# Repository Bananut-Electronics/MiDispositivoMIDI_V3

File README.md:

<h1 align="center"> ⭐️ MiDispositivoMIDI V3 ⭐️ </h1>

*This repository is no longer officially maintained but feel free to open a pull request with your contribution. As we ran out of devices, we don't sell it anymore, but if you you want one you can find here all the schematics, manuals, documentations and code to build your own.*
<!-- ALL-CONTRIBUTORS-BADGE:START - Do not remove or modify this section -->

<!-- ALL-CONTRIBUTORS-BADGE:END -->

<p align="center">

<p align="center">
  Connect our device to your computer and start making music! Totally Plug&Play without any extra software, just your favourite MIDI sequencer (Logic, Ableto, Nuendo). It is not only a great tool for making music and experimenting, you can also use it to learn more about electronics, programming and Arduino. You have tons of code examples ready to load, but if you feel up to it, you can also contribute with your code. And last but not least! It is open source! You can either buy it at our website, our build it yourself, all the schematics and code are available in this repository.
  <p align="center">
  
</p>
</p>

---

<h2 align="center">❤️ Follow us! ❤️</h2>
<p align="center">

</p>

---

<h2 align="center">💶 Want to buy the product? 💶</h2>

<p align="center">
  
</p>

---

<h2 align="center">📗 Index 📗</h2>

<p align="center">
  <a href="#about-us">About us</a> •
  <a href="#midispositivomidi-v3">MiDispositivoMIDI V3</a> •
  <a href="#documentation">Documentation</a> •
  <a href="#expansions">Expansions</a> •
  <a href="#faq">FAQ</a> •
  <a href="#contributing">Contributing</a> •
  <a href="#license">License</a>
</p>

---

# About us
Hi! We are BanaNut Electronics and we develop software and hardware for Arduino with educational purposes. We were born at the UPM University in Madrid during 2013 and we haven't stopped ever since.

<center>

|      LightWand Kosmonaut V2      |  MiDispositivoMIDI V3 |
|:-------------:|:------:|
|   |  |

</center>

---

Everything started with the first version at the Polytechnical University of Madrid (UPM) in 2013. We were a couple of young students interested in music and electronics, and we came up with this idea. We started reusing some hardware, mainly found at SparkFun's website, but only one year later, we had the second version that was fully designed by us. After some trial and error and feedback from users and friends, we released this third version V3 in 2017. We not only released the code, but also we started producing devices and selling them on the internet, first in our web and later on at Tindie.com store.

During the years, the different versions of MiDispositivoMIDI have been used by many people, engineers, musicians and even kids. We gave some workshops at UPM Madrid for students in Electrical and Telecommunications Engineering, where we gave all the materials and the students had to solder, assembly and code the device.

<p align="center">
  
</a>

---

# MiDispositivoMIDI V3
We are proud to present the MiDispositivoMIDI V3, which is the latest version we have out in the market (Jan 2019). MiDispositivoMIDI is an open source MIDI controller based on Arduino. In other words, its a small device with tons of LEDs and buttons, that you can connect to your computer to, in example, make music. Our device works with the MIDI protocol, a very well known protocol used in the music industry. You can just plug our device and start using it with your favourite DAW, such as Logic, Ableton or Cubase. No other extra softare is needed.

If you are also interested in programming and electronics, this device offer you a great tool to learn by example. You can also use it to prototype and play around. And also, since it is open source you can fully costumize it to your needs. If you don't know much about coding, just load the codes that we provide, and use them. But if you like coding, you can also publish your code with new features or improvements for others to use.

<p align="center">

<p align="center">

These are the features of our device:
* Plug & Play MIDI device.
* Open source based on Arduino.
* Have 16 pad buttons in a 4x4 matrix.
* Have 2 lateral buttons.
* Have RGB leds with 256 levels of intensity of each color.
* Micro USB connection.
* Dimensions of 10x10 cm.
* Modular design. Connect up to 4 devices.
* Fully compatible with Logic, Ableton or Cubase.

<p align="center">
  
</a>

We invite you to check our YouTube channel, where we post videos about our devices. You can also follow other social networks such as Instagram o Facebook.

* https://www.youtube.com/watch?v=3QnzLwpbpRE&t
* https://www.youtube.com/watch?v=8WFfShg-0Dk
* https://www.youtube.com/watch?v=2y8fhmTmedI
* https://www.youtube.com/watch?v=TsuVpFoLFyI

---

# Documentation

We provide a C++ Arduino library that you can use with our device, that simplifies the tasks of handling the LEDs and buttons. The code is self documented, but we have also written a nice Wiki page where you can find more information about the hardware, some hints about MIDI protocol and some low level software examples in Arduino, that will allow you to understand how it works:
* Wiki: https://github.com/Bananut-Electronics/MiDispositivoMIDI_V3/wiki

TODO: Write some nice code snippets
```cpp
//TODO
```

---

# Expansions

Our device has a modular design, which means that with the same hardware, you can add modules to convert it into a bigger controller. For example, if you put four MiDispositivoMIDI V3 into a 8x8 configuration, you will have 64 buttons. All this can be done using the same hardware and with very few modificatons in the code. Note that you can also replace a 4x4 button matrix by a 4x4 potentiometer matrix, but this feature is not implemented yet.

<p align="center">

## 4x16 Configuration

You can connect 4 MiDispositivoMIDI V3 in a 4x16 configuration to get the following. With something like this, you can, for example, create an step sequencer. See this video for an example:
* https://www.youtube.com/watch?v=bYyvVDn-gKs

<p align="center">
  
</a>

## 8x8 Configuration
Same as before, you can connect the devices with a different configuration. Note that the connections are done under the PCB with an extra PCB, so no extra wiring is needed.

<p align="center">
  
</a>

## 4x8 Configuration
TODO

## Potentiometer Expansion
TODO

---

# FAQ

Feel free to send us a mail to bananutelectronics@gmail.com if you have any question, but read before our FAQ since there are some common issues that can be fixed quite easily:

* **I can't load code to my device. Why?** Make sure that in the Arduino IDE boards section (Tool->Boards) you have selected "Arduino Leonardo"
* **I was playing with some code, and now the device is gone form the serial port list. Why?** If you were playing with some experimental code, you might have screwed up the "operative system" of the Arduino. But no worries, the fix is pretty straightforward. Open an example from the basic library (i.e. Examples->Basics-Blink) and hit the "Upload" button. You will first see that it is "Compiling" and that that is "Loading". Click the reset button right after "Compiling" is finished. With this you should get the bootloader running and you will be able to load the code. After this, you should be able to see the device in the serial port list as usual. Note that the reset button is the one on the top (not the ones on the left).
* **When I press a button, the LED takes a bit to light up, why?** There should not be any delay when you press a button, so right after pressing the pad, you should see that it lights up (assuming of course that it configured to do so). If this delay is present, please, make sure that you have a MIDI program reading the port in your computer.

---

# Contributing
Feel free to create a pull request with your new feature, we will be pleased to add it to our repo. We can differentiate between three different types of contributions:

* Contributing to the Arduino library: Feel free to add stuff related to our Arduino library in the `src` folder. Note that if you add a new feature to our library, we would love to see also a working example in the `examples` folder using that new functionality. Name if as `MDM_V3_Library_xxx` so that we know that that code uses the library.
* Contributing with new examples: You can add code inside the `examples` folder. Just remember to name it with `MDM_V3_NoLibrary_xxx` if that code is not using any function provided by the library.
* Other random stuff: Feel free to add images with your own setup, correct existing code, fix bugs or whatever you have in mind.

---

# License

<br /><span xmlns:dct="http://purl.org/dc/terms/" property="dct:title">MiDispositivoMIDI</span> by <a xmlns:cc="http://creativecommons.org/ns#" href="www.bananutelectronics.com" property="cc:attributionName" rel="cc:attributionURL">Alvaro Lopez & Pablo de Miguel Morales</a> is licensed under a <a rel="license" href="http://creativecommons.org/licenses/by-nc-sa/4.0/">Creative Commons Attribution-NonCommercial-ShareAlike 4.0 International License</a>.<br />

## Contributors ✨

Thanks goes to these wonderful people ([emoji key](https://allcontributors.org/docs/en/emoji-key)):

<!-- ALL-CONTRIBUTORS-LIST:START - Do not remove or modify this section -->
<!-- prettier-ignore-start -->
<!-- markdownlint-disable -->
<table>
  <tr>
    <td align="center"><a href="https://github.com/pabloEntropia"><br /><sub><b>Pablo Alonso</b></sub></a><br /><a href="https://github.com/Bananut-Electronics/MiDispositivoMIDI_V3/commits?author=pabloEntropia" title="Code">💻</a></td>
    <td align="center"><a href="https://github.com/per1234"><br /><sub><b>per1234</b></sub></a><br /><a href="https://github.com/Bananut-Electronics/MiDispositivoMIDI_V3/commits?author=per1234" title="Code">💻</a></td>
  </tr>
</table>

<!-- markdownlint-enable -->
<!-- prettier-ignore-end -->
<!-- ALL-CONTRIBUTORS-LIST:END -->

This project follows the [all-contributors](https://github.com/all-contributors/all-contributors) specification. Contributions of any kind welcome!

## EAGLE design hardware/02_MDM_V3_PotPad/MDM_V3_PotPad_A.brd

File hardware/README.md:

# Hardware

## Led Pad
Upper PCB, contains 16 leds LEDs and pad buttons

## Control Board
Lower PCB, contains the Arduino

## Pot Pad
Potentiometer expansion. **Important** This board is not officially supported yet and there might be a bug with some swapped pins. Do not send for production.

## Connector
Connects Pot Pads expansions.

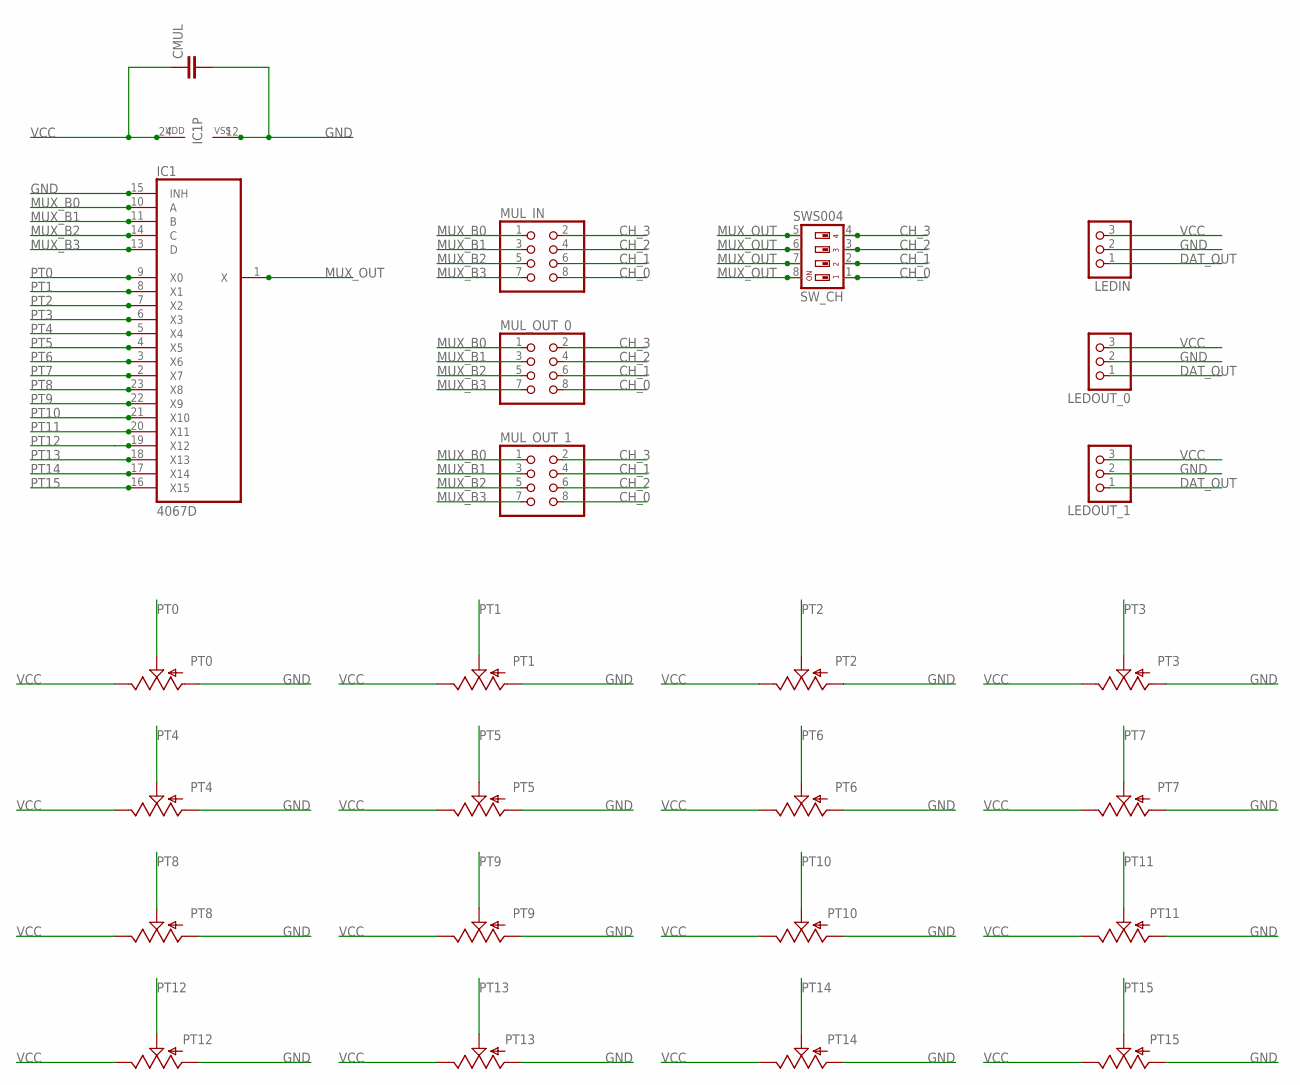
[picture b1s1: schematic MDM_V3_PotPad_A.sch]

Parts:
CMUL: C-EUC1206K; C1206K
IC1: 4067D; SO24W
LEDIN: PINHD-1X3; 1X03
LEDOUT_0, LEDOUT_1: PINHD-1X3; 1X03
MUL_IN: PINHD-2X4; 2X04
MUL_OUT_0, MUL_OUT_1: PINHD-2X4; 2X04
PT0, PT1, PT2, PT3, PT4, PT5, PT6, PT7, PT8, PT9, PT10, PT11, PT12, PT13, PT14, PT15: POT; ALPS_POT
SW_CH: SWS004; SMS-004

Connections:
CH_0: MUL_IN.8, MUL_OUT_0.8, MUL_OUT_1.8, SW_CH.1
CH_1: MUL_IN.6, MUL_OUT_0.6, MUL_OUT_1.4, SW_CH.2
CH_2: MUL_IN.4, MUL_OUT_0.4, MUL_OUT_1.6, SW_CH.3
CH_3: MUL_IN.2, MUL_OUT_0.2, MUL_OUT_1.2, SW_CH.4
DAT_OUT: LEDIN.1, LEDOUT_0.1, LEDOUT_1.1
GND: CMUL.2, IC1.12 (VSS), IC1.15 (INH), LEDIN.2, LEDOUT_0.2, LEDOUT_1.2, PT0.P$3 (A), PT1.P$3 (A), PT2.P$3 (A), PT3.P$3 (A), PT4.P$3 (A), PT5.P$3 (A), PT6.P$3 (A), PT7.P$3 (A), PT8.P$3 (A), PT9.P$3 (A), PT10.P$3 (A), PT11.P$3 (A), PT12.P$3 (A), PT13.P$3 (A), PT14.P$3 (A), PT15.P$3 (A)
MUX_B0: IC1.10 (A), MUL_IN.1, MUL_OUT_0.1, MUL_OUT_1.1
MUX_B1: IC1.11 (B), MUL_IN.3, MUL_OUT_0.3, MUL_OUT_1.3
MUX_B2: IC1.14 (C), MUL_IN.5, MUL_OUT_0.5, MUL_OUT_1.5
MUX_B3: IC1.13 (D), MUL_IN.7, MUL_OUT_0.7, MUL_OUT_1.7
MUX_OUT: IC1.1 (X), SW_CH.5, SW_CH.6, SW_CH.7, SW_CH.8
PT0: IC1.9 (X0), PT0.P$2 (S)
PT1: IC1.8 (X1), PT1.P$2 (S)
PT2: IC1.7 (X2), PT2.P$2 (S)
PT3: IC1.6 (X3), PT3.P$2 (S)
PT4: IC1.5 (X4), PT4.P$2 (S)
PT5: IC1.4 (X5), PT5.P$2 (S)
PT6: IC1.3 (X6), PT6.P$2 (S)
PT7: IC1.2 (X7), PT7.P$2 (S)
PT8: IC1.23 (X8), PT8.P$2 (S)
PT9: IC1.22 (X9), PT9.P$2 (S)
PT10: IC1.21 (X10), PT10.P$2 (S)
PT11: IC1.20 (X11), PT11.P$2 (S)
PT12: IC1.19 (X12), PT12.P$2 (S)
PT13: IC1.18 (X13), PT13.P$2 (S)
PT14: IC1.17 (X14), PT14.P$2 (S)
PT15: IC1.16 (X15), PT15.P$2 (S)
VCC: CMUL.1, IC1.24 (VDD), LEDIN.3, LEDOUT_0.3, LEDOUT_1.3, PT0.P$1 (E), PT1.P$1 (E), PT2.P$1 (E), PT3.P$1 (E), PT4.P$1 (E), PT5.P$1 (E), PT6.P$1 (E), PT7.P$1 (E), PT8.P$1 (E), PT9.P$1 (E), PT10.P$1 (E), PT11.P$1 (E), PT12.P$1 (E), PT13.P$1 (E), PT14.P$1 (E), PT15.P$1 (E)

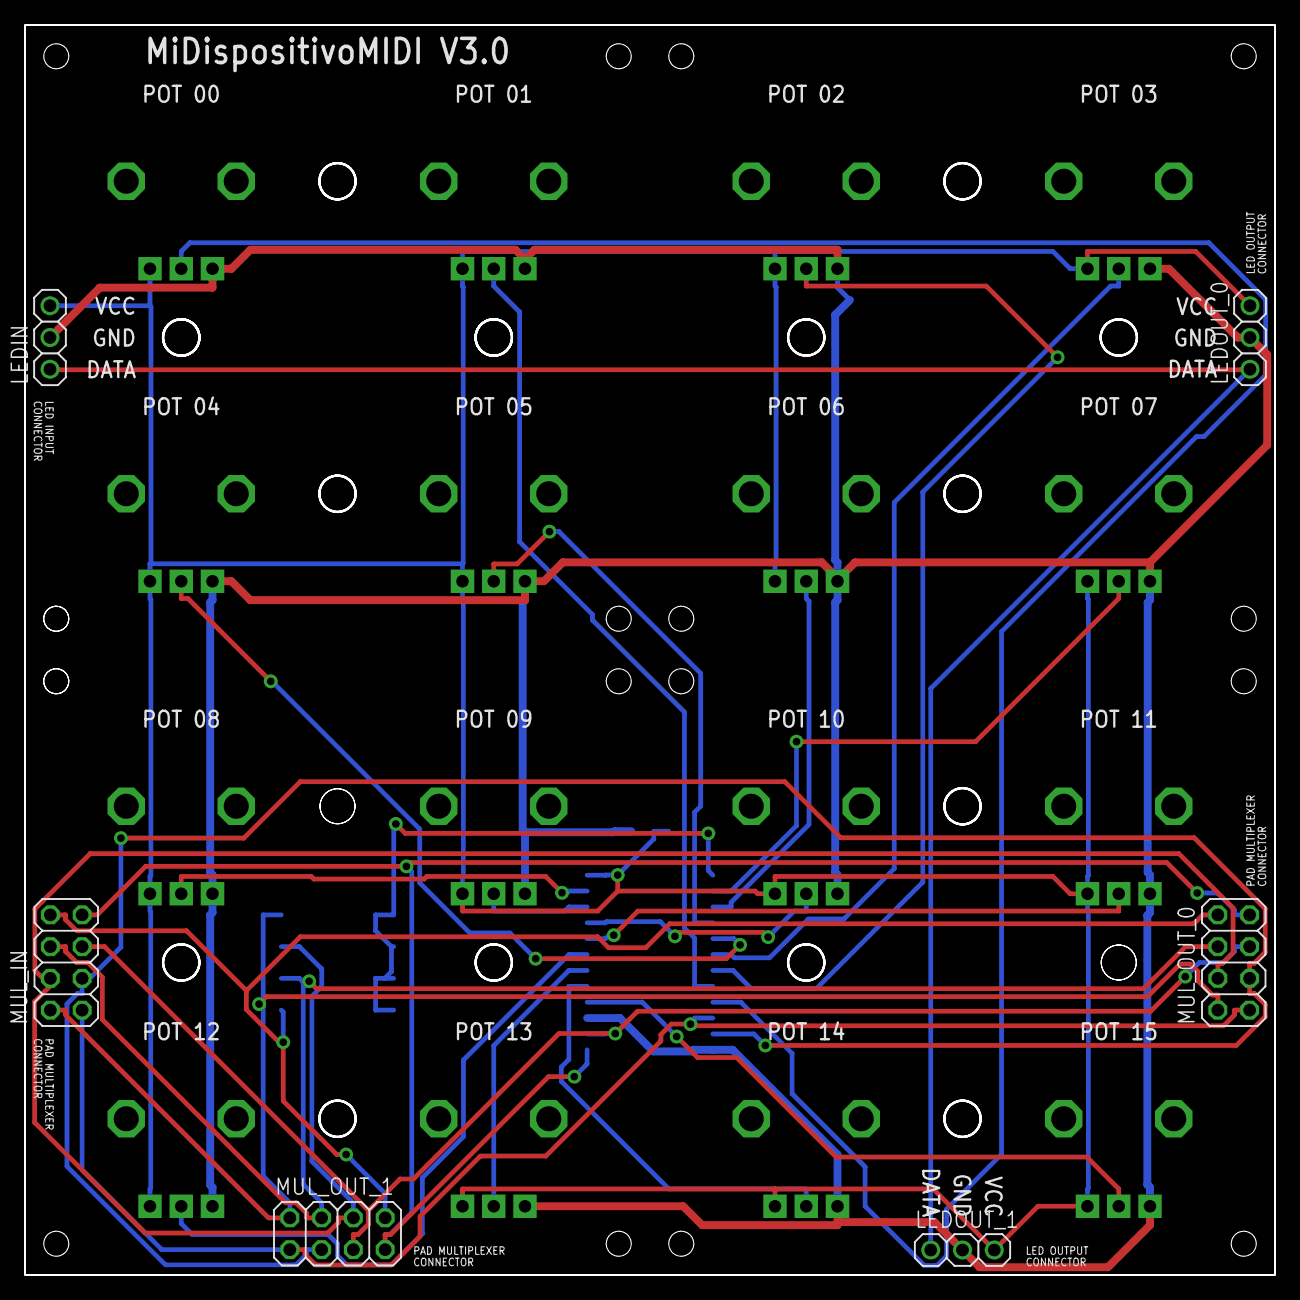
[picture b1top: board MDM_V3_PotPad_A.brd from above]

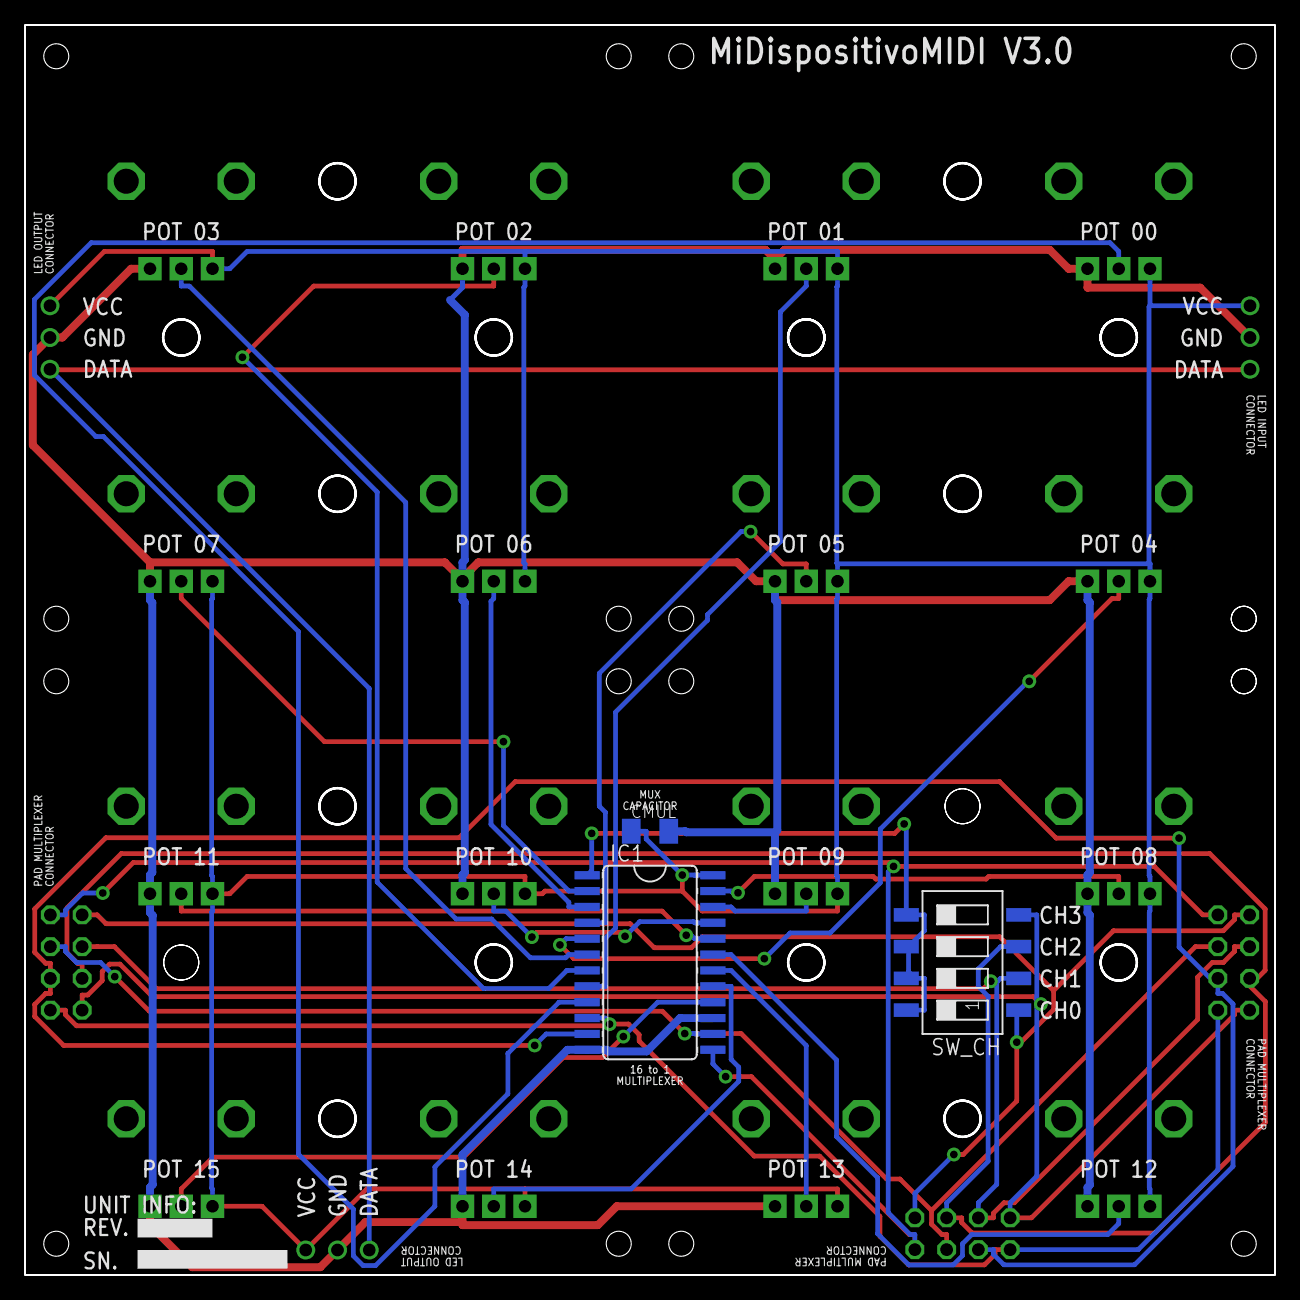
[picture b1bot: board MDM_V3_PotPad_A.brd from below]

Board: 2 copper layers, 100.0 x 100.0 mm, 25 parts (3 on the bottom side), 28 nets.

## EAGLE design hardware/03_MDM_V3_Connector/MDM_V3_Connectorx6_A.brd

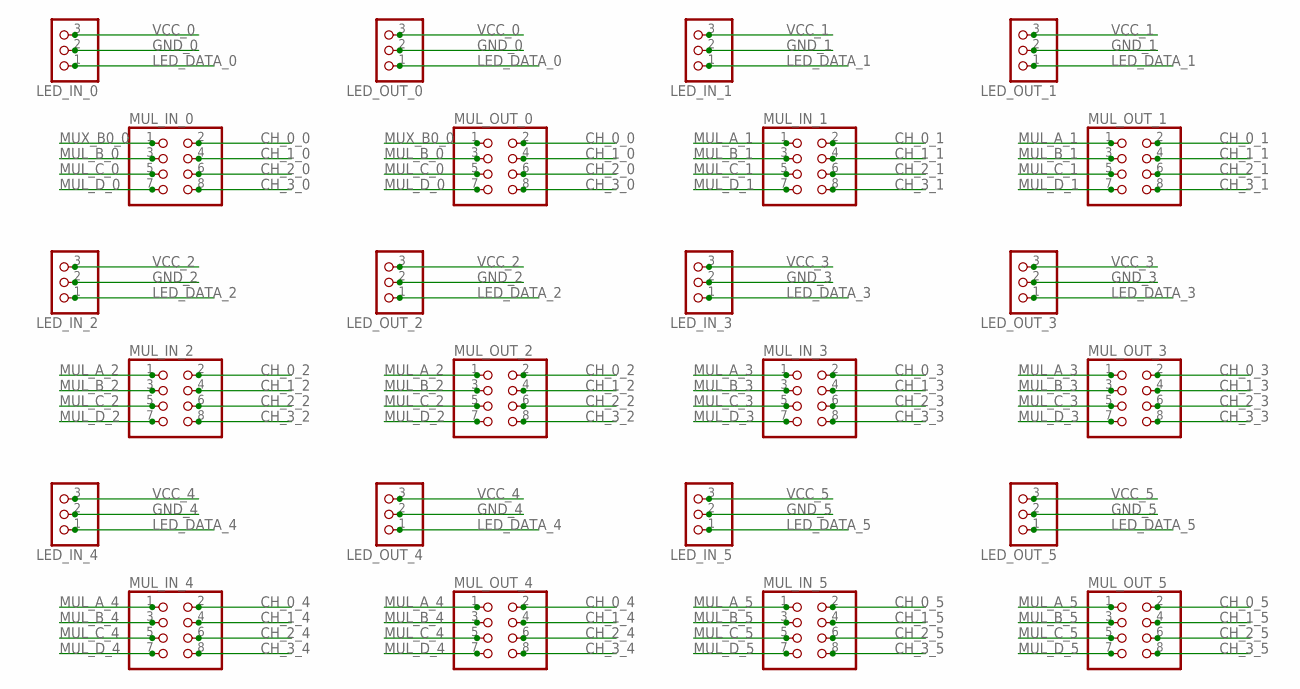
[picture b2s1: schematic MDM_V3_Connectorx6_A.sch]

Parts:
LED_IN_0, LED_IN_1, LED_IN_2, LED_IN_3, LED_IN_4, LED_IN_5: PINHD-1X3; 1X03
LED_OUT_0, LED_OUT_1, LED_OUT_2, LED_OUT_3, LED_OUT_4, LED_OUT_5: PINHD-1X3; 1X03
MUL_IN_0, MUL_IN_1, MUL_IN_2, MUL_IN_3, MUL_IN_4, MUL_IN_5: PINHD-2X4; 2X04
MUL_OUT_0, MUL_OUT_1, MUL_OUT_2, MUL_OUT_3, MUL_OUT_4, MUL_OUT_5: PINHD-2X4; 2X04

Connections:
CH_0_0: MUL_IN_0.2, MUL_OUT_0.2
CH_0_1: MUL_IN_1.2, MUL_OUT_1.2
CH_0_2: MUL_IN_2.2, MUL_OUT_2.2
CH_0_3: MUL_IN_3.2, MUL_OUT_3.2
CH_0_4: MUL_IN_4.2, MUL_OUT_4.2
CH_0_5: MUL_IN_5.2, MUL_OUT_5.2
CH_1_0: MUL_IN_0.4, MUL_OUT_0.4
CH_1_1: MUL_IN_1.4, MUL_OUT_1.4
CH_1_2: MUL_IN_2.4, MUL_OUT_2.4
CH_1_3: MUL_IN_3.4, MUL_OUT_3.4
CH_1_4: MUL_IN_4.4, MUL_OUT_4.4
CH_1_5: MUL_IN_5.4, MUL_OUT_5.4
CH_2_0: MUL_IN_0.6, MUL_OUT_0.6
CH_2_1: MUL_IN_1.6, MUL_OUT_1.6
CH_2_2: MUL_IN_2.6, MUL_OUT_2.6
CH_2_3: MUL_IN_3.6, MUL_OUT_3.6
CH_2_4: MUL_IN_4.6, MUL_OUT_4.6
CH_2_5: MUL_IN_5.6, MUL_OUT_5.6
CH_3_0: MUL_IN_0.8, MUL_OUT_0.8
CH_3_1: MUL_IN_1.8, MUL_OUT_1.8
CH_3_2: MUL_IN_2.8, MUL_OUT_2.8
CH_3_3: MUL_IN_3.8, MUL_OUT_3.8
CH_3_4: MUL_IN_4.8, MUL_OUT_4.8
CH_3_5: MUL_IN_5.8, MUL_OUT_5.8
GND_0: LED_IN_0.2, LED_OUT_0.2
GND_1: LED_IN_1.2, LED_OUT_1.2
GND_2: LED_IN_2.2, LED_OUT_2.2
GND_3: LED_IN_3.2, LED_OUT_3.2
GND_4: LED_IN_4.2, LED_OUT_4.2
GND_5: LED_IN_5.2, LED_OUT_5.2
LED_DATA_0: LED_IN_0.1, LED_OUT_0.1
LED_DATA_1: LED_IN_1.1, LED_OUT_1.1
LED_DATA_2: LED_IN_2.1, LED_OUT_2.1
LED_DATA_3: LED_IN_3.1, LED_OUT_3.1
LED_DATA_4: LED_IN_4.1, LED_OUT_4.1
LED_DATA_5: LED_IN_5.1, LED_OUT_5.1
MUL_A_1: MUL_IN_1.1, MUL_OUT_1.1
MUL_A_2: MUL_IN_2.1, MUL_OUT_2.1
MUL_A_3: MUL_IN_3.1, MUL_OUT_3.1
MUL_A_4: MUL_IN_4.1, MUL_OUT_4.1
MUL_A_5: MUL_IN_5.1, MUL_OUT_5.1
MUL_B_0: MUL_IN_0.3, MUL_OUT_0.3
MUL_B_1: MUL_IN_1.3, MUL_OUT_1.3
MUL_B_2: MUL_IN_2.3, MUL_OUT_2.3
MUL_B_3: MUL_IN_3.3, MUL_OUT_3.3
MUL_B_4: MUL_IN_4.3, MUL_OUT_4.3
MUL_B_5: MUL_IN_5.3, MUL_OUT_5.3
MUL_C_0: MUL_IN_0.5, MUL_OUT_0.5
MUL_C_1: MUL_IN_1.5, MUL_OUT_1.5
MUL_C_2: MUL_IN_2.5, MUL_OUT_2.5
MUL_C_3: MUL_IN_3.5, MUL_OUT_3.5
MUL_C_4: MUL_IN_4.5, MUL_OUT_4.5
MUL_C_5: MUL_IN_5.5, MUL_OUT_5.5
MUL_D_0: MUL_IN_0.7, MUL_OUT_0.7
MUL_D_1: MUL_IN_1.7, MUL_OUT_1.7
MUL_D_2: MUL_IN_2.7, MUL_OUT_2.7
MUL_D_3: MUL_IN_3.7, MUL_OUT_3.7
MUL_D_4: MUL_IN_4.7, MUL_OUT_4.7
MUL_D_5: MUL_IN_5.7, MUL_OUT_5.7
MUX_B0_0: MUL_IN_0.1, MUL_OUT_0.1
VCC_0: LED_IN_0.3, LED_OUT_0.3
VCC_1: LED_IN_1.3, LED_OUT_1.3
VCC_2: LED_IN_2.3, LED_OUT_2.3
VCC_3: LED_IN_3.3, LED_OUT_3.3
VCC_4: LED_IN_4.3, LED_OUT_4.3
VCC_5: LED_IN_5.3, LED_OUT_5.3

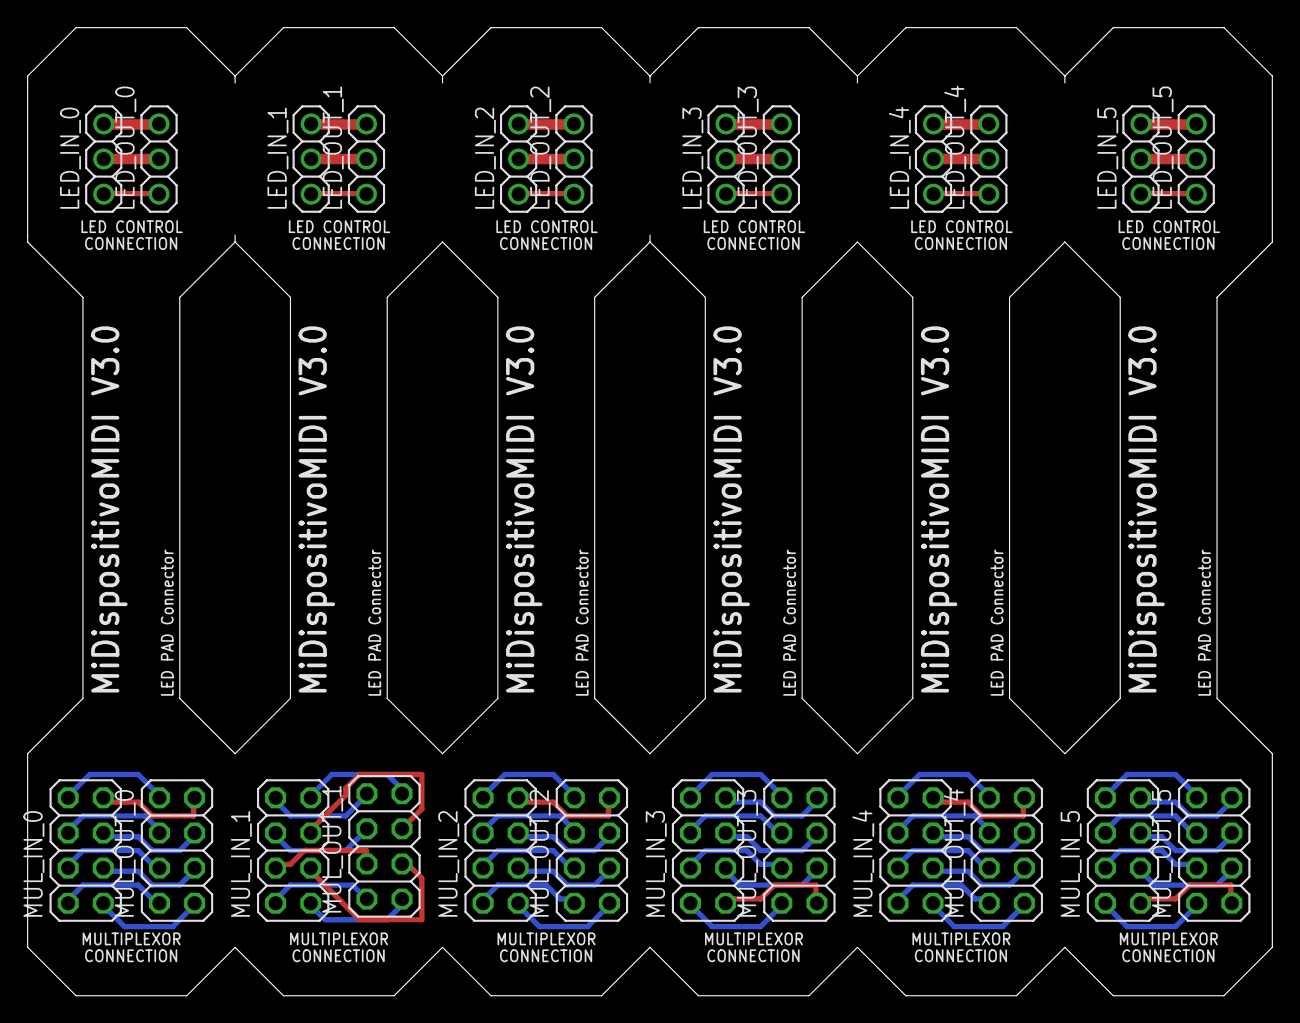
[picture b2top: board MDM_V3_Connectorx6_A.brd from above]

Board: 2 copper layers, 90.0 x 70.0 mm, 24 parts (0 on the bottom side), 66 nets.

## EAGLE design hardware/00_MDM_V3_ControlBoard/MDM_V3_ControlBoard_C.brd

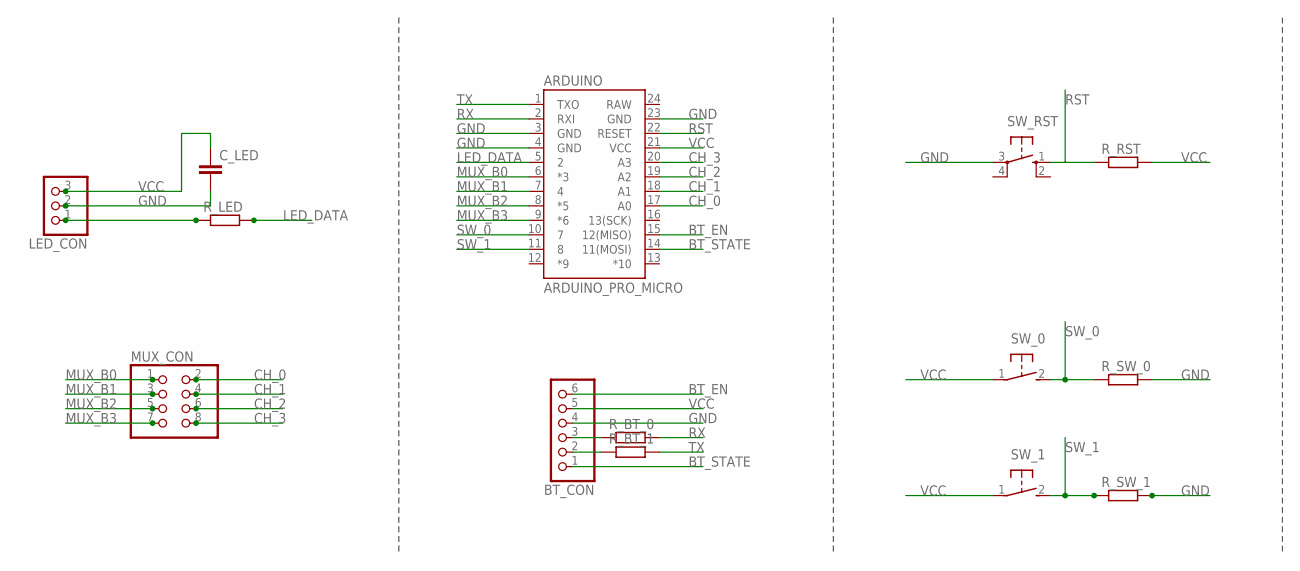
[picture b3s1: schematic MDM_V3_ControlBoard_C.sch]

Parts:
ARDUINO: ARDUINO_PRO_MICRO
BT_CON: PINHD-1X6; 1X06
C_LED: C-EUC1206K; C1206K
LED_CON: PINHD-1X3; 1X03
MUX_CON: PINHD-2X4; 2X04
R_BT_0, R_BT_1: R-EU_M1206; M1206
R_LED: R-EU_M1206; M1206
R_RST: R-EU_M1206; M1206
R_SW_0, R_SW_1: R-EU_M1206; M1206
SW_0, SW_1: 31-XX; B3F-31XX
SW_RST: 10-XX; B3F-10XX

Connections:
BT_EN: ARDUINO.15 (12(MISO)), BT_CON.6
BT_STATE: ARDUINO.14 (11(MOSI)), BT_CON.1
CH_0: ARDUINO.17 (A0), MUX_CON.2
CH_1: ARDUINO.18 (A1), MUX_CON.4
CH_2: ARDUINO.19 (A2), MUX_CON.6
CH_3: ARDUINO.20 (A3), MUX_CON.8
GND: ARDUINO.3 (GND), ARDUINO.4 (GND), ARDUINO.23 (GND), BT_CON.4, C_LED.2, LED_CON.2, R_SW_0.2, R_SW_1.2, SW_RST.3
LED_DATA: ARDUINO.5 (2), R_LED.2
MUX_B0: ARDUINO.6 (*3), MUX_CON.1
MUX_B1: ARDUINO.7 (4), MUX_CON.3
MUX_B2: ARDUINO.8 (*5), MUX_CON.5
MUX_B3: ARDUINO.9 (*6), MUX_CON.7
unnamed: BT_CON.2, R_BT_1.1
unnamed: BT_CON.3, R_BT_0.1
unnamed: LED_CON.1, R_LED.1
RST: ARDUINO.22 (RESET), R_RST.1, SW_RST.1 (S)
RX: ARDUINO.2 (RXI), R_BT_0.2
SW_0: ARDUINO.10 (7), R_SW_0.1, SW_0.2 (S)
SW_1: ARDUINO.11 (8), R_SW_1.1, SW_1.2 (S)
TX: ARDUINO.1 (TXO), R_BT_1.2
VCC: ARDUINO.21 (VCC), BT_CON.5, C_LED.1, LED_CON.3, R_RST.2, SW_0.1, SW_1.1

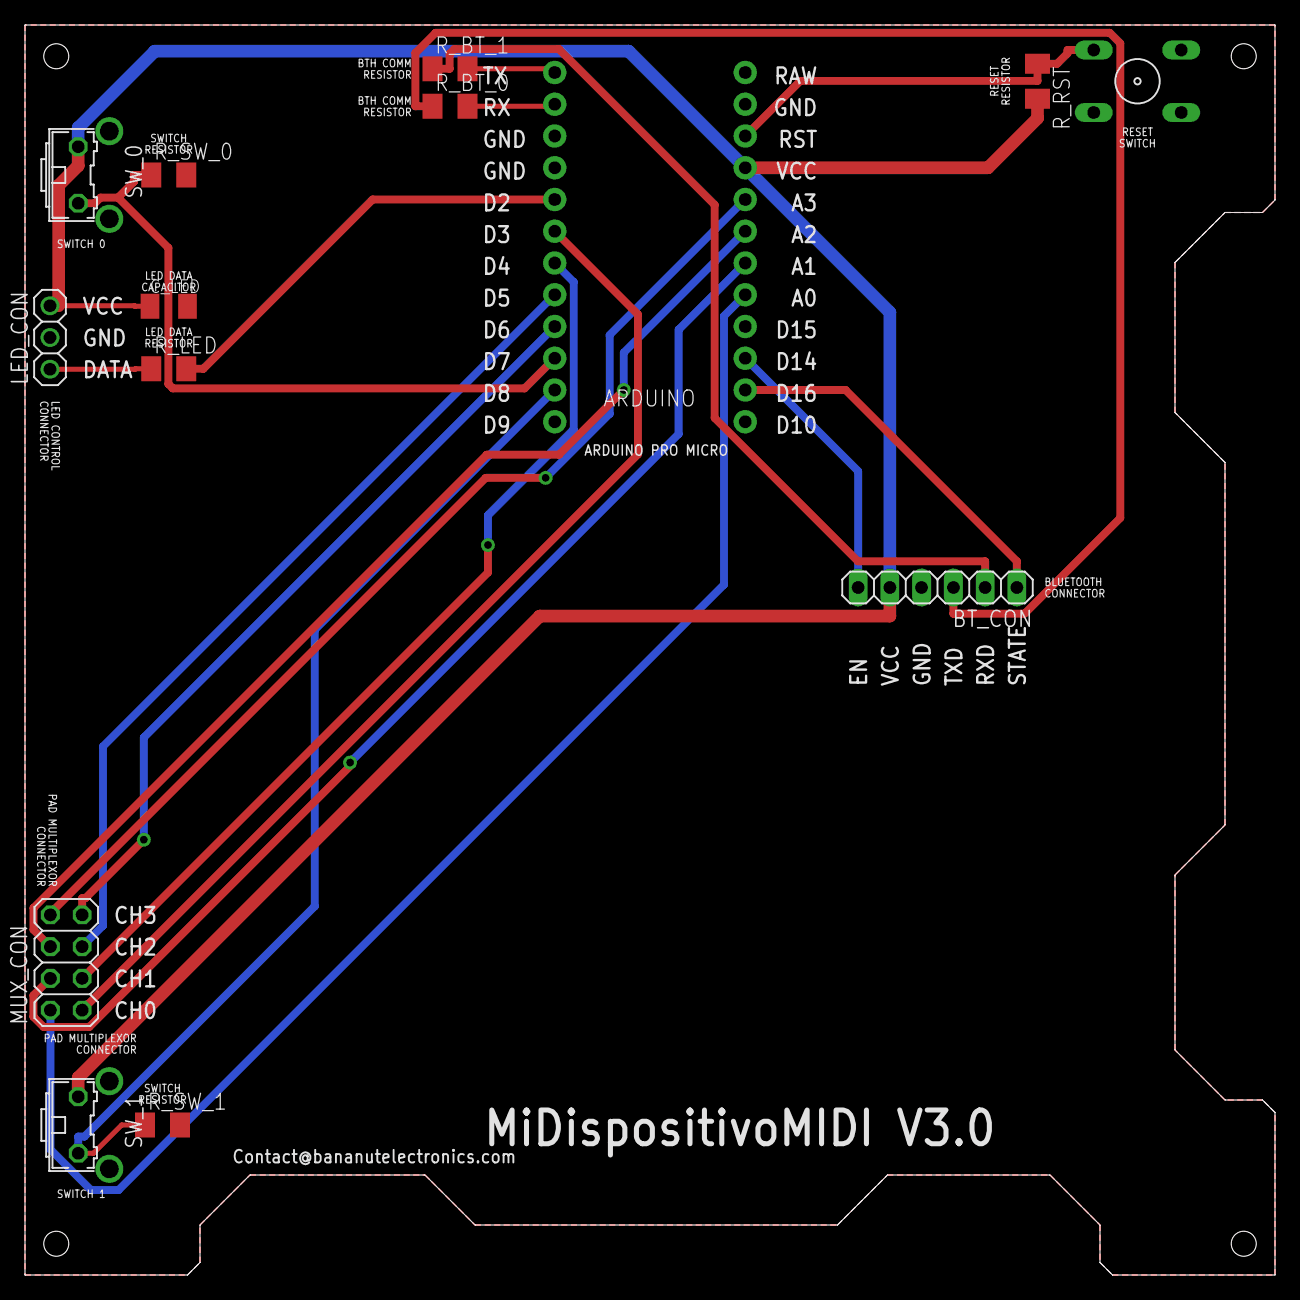
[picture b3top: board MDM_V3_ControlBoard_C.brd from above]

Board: 2 copper layers, 100.0 x 100.0 mm, 14 parts (0 on the bottom side), 21 nets.

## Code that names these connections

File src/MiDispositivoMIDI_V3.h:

/*
  2018 BanaNut Electronics (bananutelectronics@gmail.com)

  This library is free software; you can redistribute it and/or
  modify it under the terms of the CC BY-NC-SA 4.0 license
  (Attribution-NonCommercial-ShareAlike 4.0 International)

  You are free to share, copy and redistribute the material in any medium
  or format, and also to adapt, remix, transform or build upon de provided
  material, always under the following terms:
    * Attribution                — You must give appropriate credit, provide a link
                                   to the license, and indicate if changes were made.
                                   You may do so in any reasonable manner, but not in any way
                                   that suggests the licensor endorses you or your use.
    * NonCommercial              — You may not use the material for commercial purposes.
    * ShareAlike                 — If you remix, transform, or build upon the material, you must
                                   distribute your contributions under the same license as the original.
    * No additional restrictions — You may not apply legal terms or technological measures that
                                   legally restrict others from doing anything the license permits.

  More informatio can be found in https://creativecommons.org/licenses/by-nc-sa/4.0/
*/

#ifndef MiDispositivoMIDI_V3_h
#define MiDispositivoMIDI_V3_h

// digital pin definition
#define LEDPAD_PIN  2
#define SW_0_PIN    7
#define SW_1_PIN    8

// analog pin definition
#define PADCH_0_PIN 0
#define PADCH_1_PIN 1
#define PADCH_2_PIN 2
#define PADCH_3_PIN 3

// mux pin definition 
#define MUX_B0_PIN 6
#define MUX_B1_PIN 5
#define MUX_B2_PIN 4
#define MUX_B3_PIN 3

// some definitions
#define N_ROWS         4
#define N_COLS         4
#define RGB_COLORS     3
#define LEDPAD_NUM     16
#define PAD_THR        500
#define MAX_EXTENSIONS 4
#define MUX_DELAY      50
#define USEC_IN_SEC    1000000
#define NUM_LATERAL_SWITCH 2

// some default values
#define DEFAULT_MIDI_CHANNEL 0
#define DEFAULT_ON_RED       0
#define DEFAULT_ON_GREEN     255
#define DEFAULT_ON_BLUE      0
#define DEFAULT_OFF_RED      255
#define DEFAULT_OFF_GREEN    255
#define DEFAULT_OFF_BLUE     255
#define DEFAULT_PAGE_NUM     0
#define DEFAULT_VELOCITY     127
#define MAX_NUMBER_OF_PAGES  4

enum HardwareConfigurations
{
  SINGLE_DEVICE_4X4,
  TWO_DEVICES_4X8,
  THREE_DEVICES_4X12,
  FOUR_DEVICES_4X16,
  FOUR_DEVICES_8X8
};

enum BoardRoles
{
  TOUCHPAD,
  POTENTIOMETER
};

class MiDispositivoMIDI_V3
{
public: 
    
    MiDispositivoMIDI_V3(HardwareConfigurations hwConfig, BoardRoles bRoles[MAX_EXTENSIONS]);
    ~MiDispositivoMIDI_V3();
    
    void loop();
    void initializeLEDs();
    void setMidiNotes(uint8_t notes[MAX_EXTENSIONS][LEDPAD_NUM]);
    void setMidiVeloc(uint8_t veloc[MAX_EXTENSIONS][LEDPAD_NUM]);
    void setOnColors(uint8_t rgbColors[RGB_COLORS]);
    void setOffColors(uint8_t rgbColors[RGB_COLORS]);
    void setPixelColor(uint8_t expansion,
                       uint8_t led,
                       uint8_t rgbColors[RGB_COLORS]);
    void setInterrupt(void (* functionPointer)(), double seconds);
    
protected:

    // when using more than one device, different configurations are possible
    HardwareConfigurations _hwConfig;

    // every 4x4 device can have buttons (PADs) or potentiometers
    BoardRoles _bRoles[MAX_EXTENSIONS];

    // number of hardware extensions [0:MAX_EXTENSIONS]
    uint8_t _numberExtensions;

    // n of rows of the hw setup, 4 for one device
    uint8_t _numOfRows;

    // n of cols of the hw setup, 4 for one device
    uint8_t _numOfCols;

    // color per led for all the device
    uint8_t _ledColors[MAX_EXTENSIONS][LEDPAD_NUM][RGB_COLORS] = {{{0}}};

    // last value read by each button
    uint8_t _lastRead[MAX_EXTENSIONS][LEDPAD_NUM]  = {{0}};

    // midi note sent by each button
    uint8_t _midiNotes[MAX_EXTENSIONS][LEDPAD_NUM] = {{0}};

    // midi velocity sent by each button
    uint8_t _midiVeloc[MAX_EXTENSIONS][LEDPAD_NUM] = {{0}};

    // default color for all leds when the button is on
    uint8_t _onColors[RGB_COLORS];

    // default color for all leds when the button is off
    uint8_t _offColors[RGB_COLORS];

    // each page sends different notes
    uint8_t _currentPage;

    void readPADs();
    void readPage();
    void updateLEDs();
    void setRgbColors(uint8_t copyFrom[RGB_COLORS],
                      uint8_t copyTo[RGB_COLORS]);

    void generateNotesVeloc(uint8_t numberOfExtensions);

    void noteOn(byte channel,
                byte pitch,
                byte velocity);

    void noteOff(byte channel,
                 byte pitch,
                 byte velocity);

    // Functions to be overrided by the user
    virtual void buttonPressed(uint8_t extension, uint8_t pad);
    virtual void buttonReleased(uint8_t extension, uint8_t pad);
    virtual void buttonHolded(uint8_t extension, uint8_t pad);
    virtual void potentiometerMoved(uint8_t extension, uint8_t pad, int value);
};

#endif

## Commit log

2019-01-23 release
2019-02-23 Release Arduino library
2019-03-04 añadido contenido UC3Music creado por Tommy Guns
2019-05-09 Fix of misspellings/typos :+1:
2019-05-28 Use correct field separator in keywords.txt
    The Arduino IDE requires the use of a single true tab separator between the keyword name and identifier. When spaces are used rather than a true tab, the keyword is not highlighted.
    Reference:
    https://github.com/arduino/Arduino/wiki/Arduino-IDE-1.5:-Library-specification#keywords
2019-07-23 Update C++ base class
    This commit tries to make MiDispositivoMIDI_V3 more flexible by
    detaching the logic that reads the PADs from the function they
    produce.
    Now readPADs produces a PADstatus {OFF, ON, ONSET, OFFSET} that is
    passed to PADaction.
    PADaction sends MIDI notes by default, but it is defined as a virtual
2019-07-23 Add prototype of Automelody example (WIP)
    This example generates melodies following a probalistic model
    generated from MIDI files. Note probabilities and transition
    probabilities are considered in the decision of the next note.
    PADs 1 to 8 will control the note generation (things like going
    up or down in the scale)
    PADs 9 to 16 will reserved for controling which scale to use,
2019-08-03 Modify library
    -Add new functions for button pressed/released/holded that can be overrided. This aims to make the device more flexible to new features.
    -Remove numPages variable from constructor, since its quite specific.
    TODO: This patch will break some examples. Fix this.
2019-08-03 Automelody improvement
    This update add the following functionalities:
    - PADs 0 to 3 generates lower notes -(I, III, IV, V)
    - PADs 4 to 7 generates higher notes +(I, III, IV, V)
    - PADs 8 to 9 are octave up/down buttons
    - PADs 10 to 11 are semitone up/down buttons
    - PADs 12 to 15 are switches for the scale. You can choose among:
2019-08-04 Add travis CI
2019-08-06 Create Gemfile
2019-08-07 Rename .travis.yaml to .travis.yml
2019-10-11 Add support for a 4x4 potentiometer extension
    Add support for a 4x4 potentiometers extension. With this new feature you can have your main 4x4 board with touch pads, and up to 3 potentiometers or touch pads extensions. All combinations are suppo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
2019-12-02 Comment buttonHolded handle
    Just comment out the buttonHolded handle.
2019-12-14 Merge master
    The API is updated to the current master version
    Next commits will update `Automelody` to comply with this version
    Main changes TODO:
    - Split PADaction() into individual actions
    - Remove note()
2019-12-19 Adapt to new API and improve behavior
    - buttons 0/7 control the range in which the new note can be selected
    - Note probs also depend on a Gaussian centered in the extreme of the
    range.
    The goal is to make the model more exprsesive by making it more likely
    to play notes that are further from the previous one
2019-12-19 Specify library dependencies in library.properties
    Specifying the library dependencies in the depends field of library.properties causes the Arduino Library Manager (Arduino IDE 1.8.10 and newer) to offer to install the dependencies during installati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
2019-12-24 Attempt to setup a simple CI
    Set up a simple CI. Just compile, no tests
2019-12-25 Create Makefile
2019-12-25 Update Makefile
2020-01-26 Add pot pad expansion (NOT OFFICIALLY SUPPORTED)
    Add pot pad expansion (NOT OFFICIALLY SUPPORTED)
2020-02-06 docs: update README.md [skip ci]
2020-02-06 docs: create .all-contributorsrc [skip ci]
2020-02-06 docs: update .all-contributorsrc [skip ci]

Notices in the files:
hardware/00_MDM_V3_ControlBoard/MDM_V3_ControlBoard_C.brd:
UNDER LICENSE
CC BY-NC-SA 4.0
parts and their libraries:
SparkFun-Boards: Licensing: Creative Commons ShareAlike 4.0 International - https://creativecommons.org/licenses/by-sa/4.0
